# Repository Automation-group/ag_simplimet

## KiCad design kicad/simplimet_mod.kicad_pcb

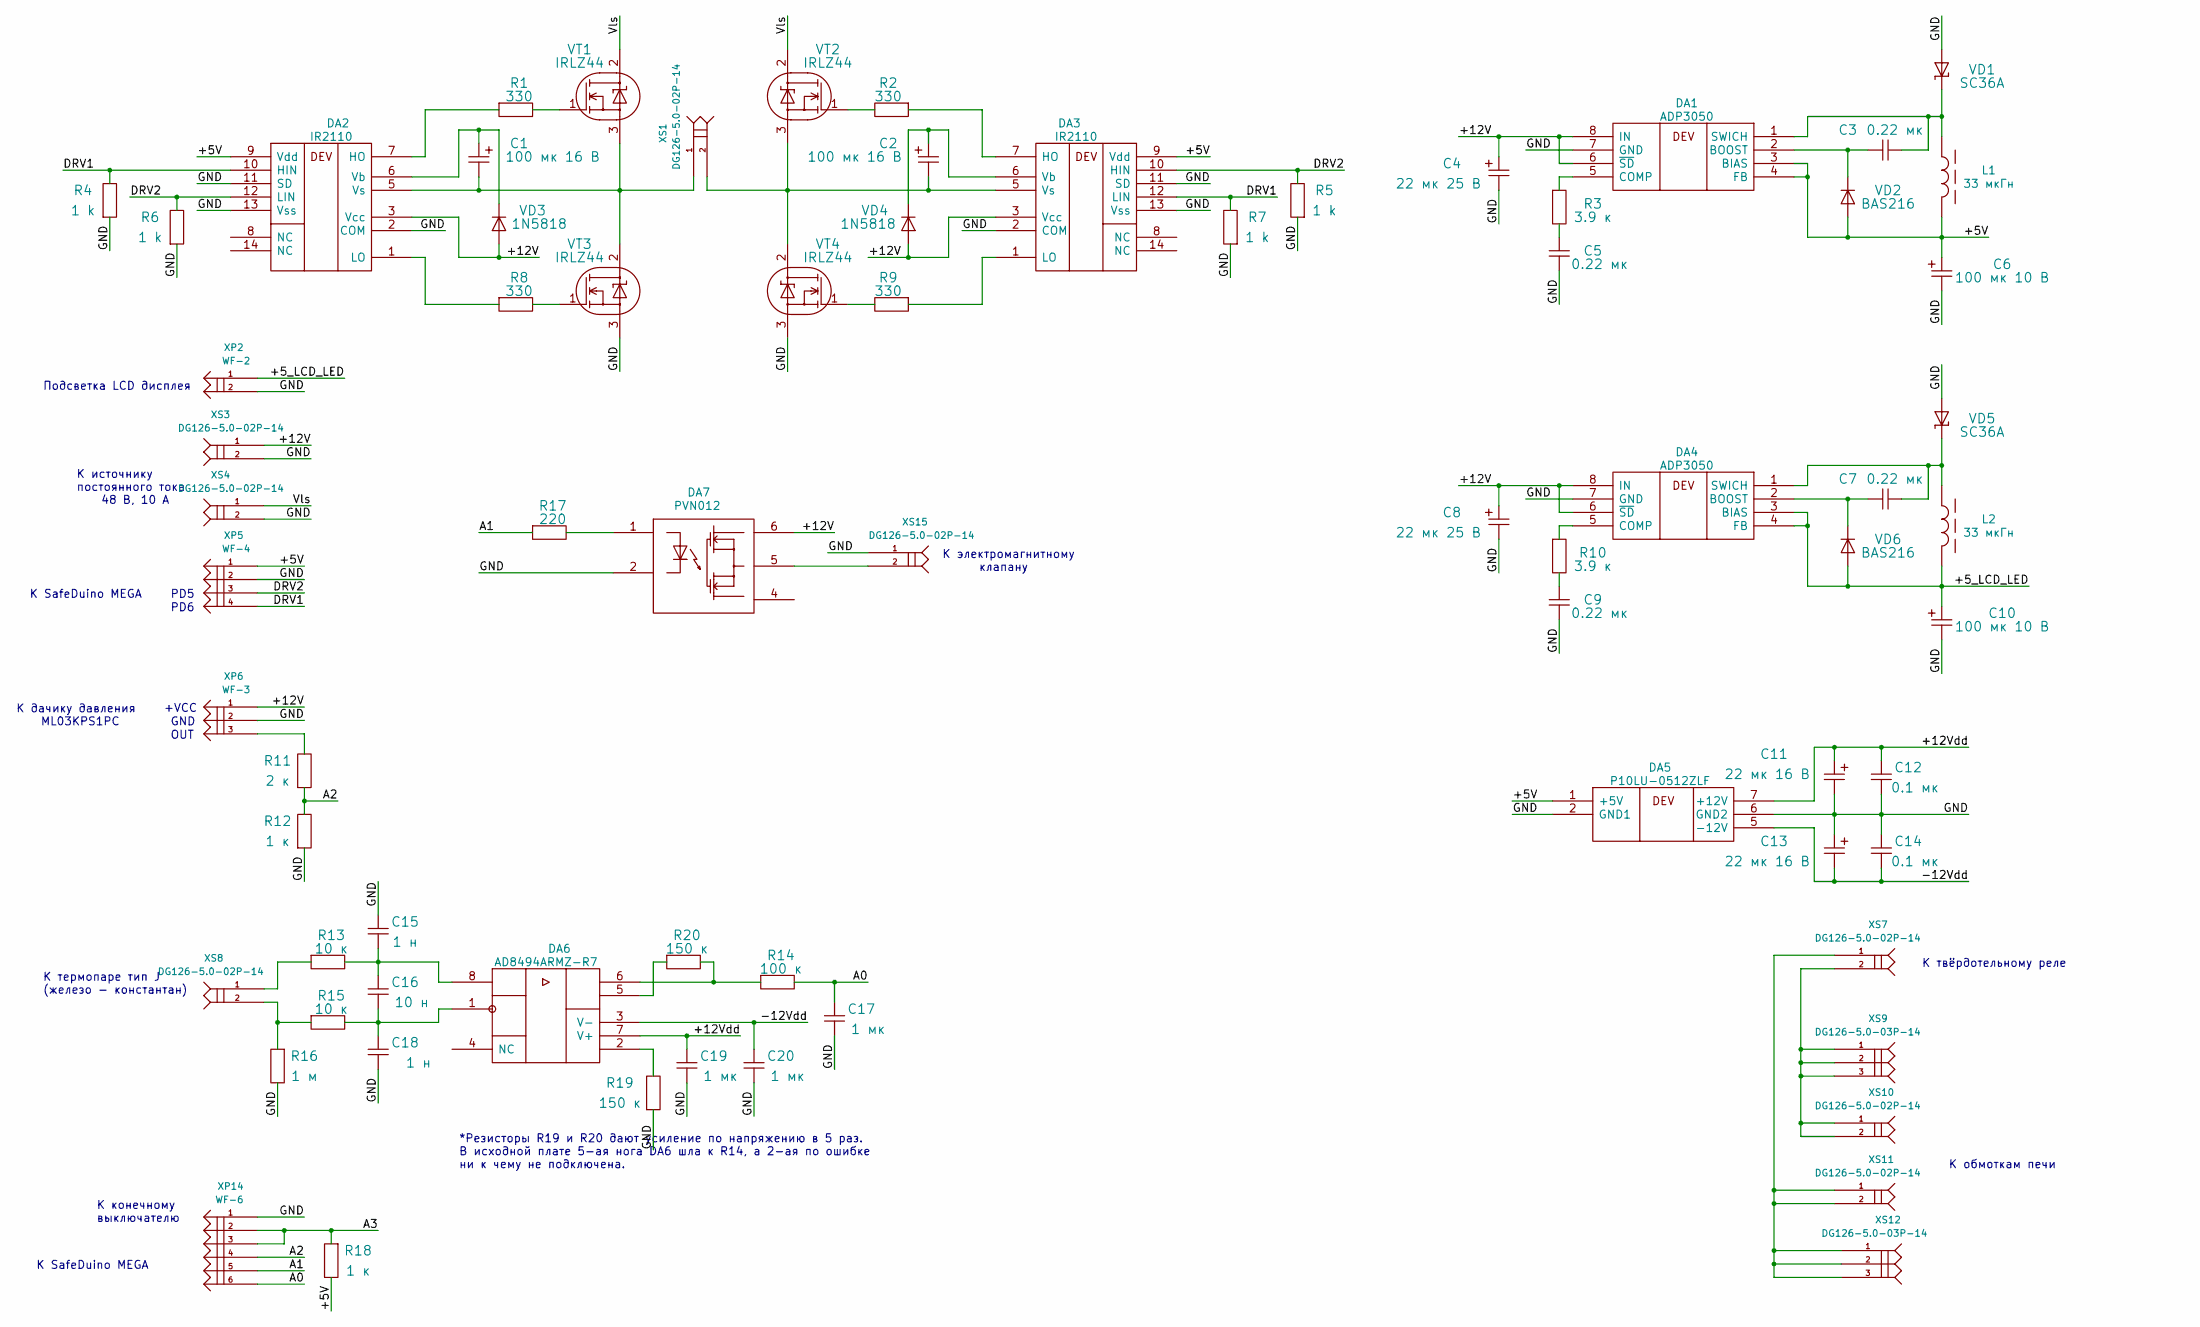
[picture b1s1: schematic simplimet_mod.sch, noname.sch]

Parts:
C1, C2: 100 мк 16 В
C3, C5, C7, C9: 0.22 мк
C4, C8: 22 мк 25 В
C6, C10: 100 мк 10 В
C11, C13: 22 мк 16 В
C12, C14: 0.1 мк
C15, C18: 1 н
C16: 10 н
C17, C19, C20: 1 мк
DA1, DA4: ADP3050
DA2, DA3: IR2110
DA5: P10LU-0512ZLF
DA6: AD8494ARMZ-R7
DA7: PVN012
L1, L2: 33 мкГн
R1, R2, R8, R9: 330
R3, R10: 3.9 к
R4, R5, R6, R7: 1 k
R11: 2 к
R12, R18: 1 к
R13, R15: 10 к
R14: 100 к
R16: 1 м
R17: 220
R19, R20: 150 к
VD1, VD5: SC36A
VD2, VD6: BAS216
VD3, VD4: 1N5818
VT1, VT2, VT3, VT4: IRLZ44
XP2: WF-2
XP5: WF-4
XP6: WF-3
XP14: WF-6
XS1, XS3, XS4, XS7, XS8, XS10, XS11, XS15: DG126-5.0-02P-14
XS9, XS12: DG126-5.0-03P-14

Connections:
/+5V: C6.1, DA1.3 (BIAS), DA1.4 (FB), DA2.9 (Vdd), DA3.9 (Vdd), DA5.1 (+5V), L1.2, R18.2, VD2.1, XP5.1
/+5_LCD_LED: C10.1, DA4.3 (BIAS), DA4.4 (FB), L2.2, VD6.1, XP2.1
/+12V: C4.1, C8.1, DA1.6 (~SD), DA1.8 (IN), DA2.3 (Vcc), DA3.3 (Vcc), DA4.6 (~SD), DA4.8 (IN), DA7.6, VD3.1, VD4.1, XP6.1, XS3.1
/+12Vdd: C11.1, C12.1, C19.1, DA5.7 (+12V), DA6.7 (V+)
/-12Vdd: C13.2, C14.2, C20.1, DA5.5 (-12V), DA6.3 (V-)
/A0: C17.1, R14.2, XP14.6
/A1: R17.1, XP14.5
/A2: R11.1, R12.2, XP14.4
/A3: R18.1, XP14.2, XP14.3
/DRV1: DA2.10 (HIN), DA3.12 (LIN), R4.2, R7.2, XP5.4
/DRV2: DA2.12 (LIN), DA3.10 (HIN), R5.2, R6.2, XP5.3
/GND: C4.2, C5.2, C6.2, C8.2, C9.2, C10.2, C11.2, C12.2, C13.1, C14.1, C15.1, C17.2, C18.2, C19.2, C20.2, DA1.7 (GND), DA2.2 (COM), DA2.11 (SD), DA2.13 (Vss), DA3.2 (COM), DA3.11 (SD), DA3.13 (Vss), DA4.7 (GND), DA5.2 (GND1), DA5.6 (GND2), DA6.2, DA7.2, R4.1, R5.1, R6.1, R7.1, R12.1, R16.2, R19.1, R19.2, VD1.1, VD5.1, VT3.3, VT4.3, XP2.2, XP5.2, XP6.2, XP14.1, XS3.2, XS4.2, XS15.1
/Vls: VT1.2, VT2.2, XS4.1
unnamed: C7.2, DA4.2 (BOOST), VD6.2
unnamed: DA1.5 (COMP), R3.1
unnamed: C5.1, R3.2
unnamed: R11.2, XP6.3
unnamed: C15.2, C16.1, DA6.8, R13.2
unnamed: C16.2, C18.1, DA6.1, R15.2
unnamed: DA4.5 (COMP), R10.1
unnamed: C7.1, DA4.1 (SWICH), L2.1, VD5.2
unnamed: C9.1, R10.2
unnamed: DA3.7 (HO), R2.1
unnamed: R2.2, VT2.1
unnamed: R9.2, VT4.1
unnamed: DA3.1 (LO), R9.1
unnamed: C3.2, DA1.2 (BOOST), VD2.2
unnamed: C3.1, DA1.1 (SWICH), L1.1, VD1.2
unnamed 28: R15.1, R16.1, XS8.2; also elsewhere on the board
unnamed: C2.1, DA3.6 (Vb), VD4.2
unnamed: C2.2, DA3.5 (Vs), VT2.3, VT4.2, XS1.2
unnamed: DA7.5, XS15.2
unnamed: DA7.1, R17.2
unnamed: XS7.1, XS11.1, XS11.2, XS12.1, XS12.2, XS12.3
unnamed 34: R13.1, XS8.1; also elsewhere on the board
unnamed: XS7.2, XS9.1, XS9.2, XS9.3, XS10.1, XS10.2
unnamed: R1.2, VT1.1
unnamed: DA2.1 (LO), R8.1
unnamed: C1.1, DA2.6 (Vb), VD3.2
unnamed: DA2.7 (HO), R1.1
unnamed: C1.2, DA2.5 (Vs), VT1.3, VT3.2, XS1.1
unnamed: R8.2, VT3.1

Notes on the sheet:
К источнику постоянного тока 48 В, 10 А
К SafeDuino MEGA
PD5
PD6
К дачику давления ML03KPS1PC
OUT
+VCC
К термопаре тип J (железо - константан)
К твёрдотельному реле
К обмоткам печи
Подсветка LCD дисплея
GND
К конечному выключателю
К электромагнитному клапану
*Резисторы R19 и R20 дают усиление по напряжению в 5 раз. В исходной плате 5-ая нога DA6 шла к R14, а 2-ая по ошибке ни к чему не подключена.

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
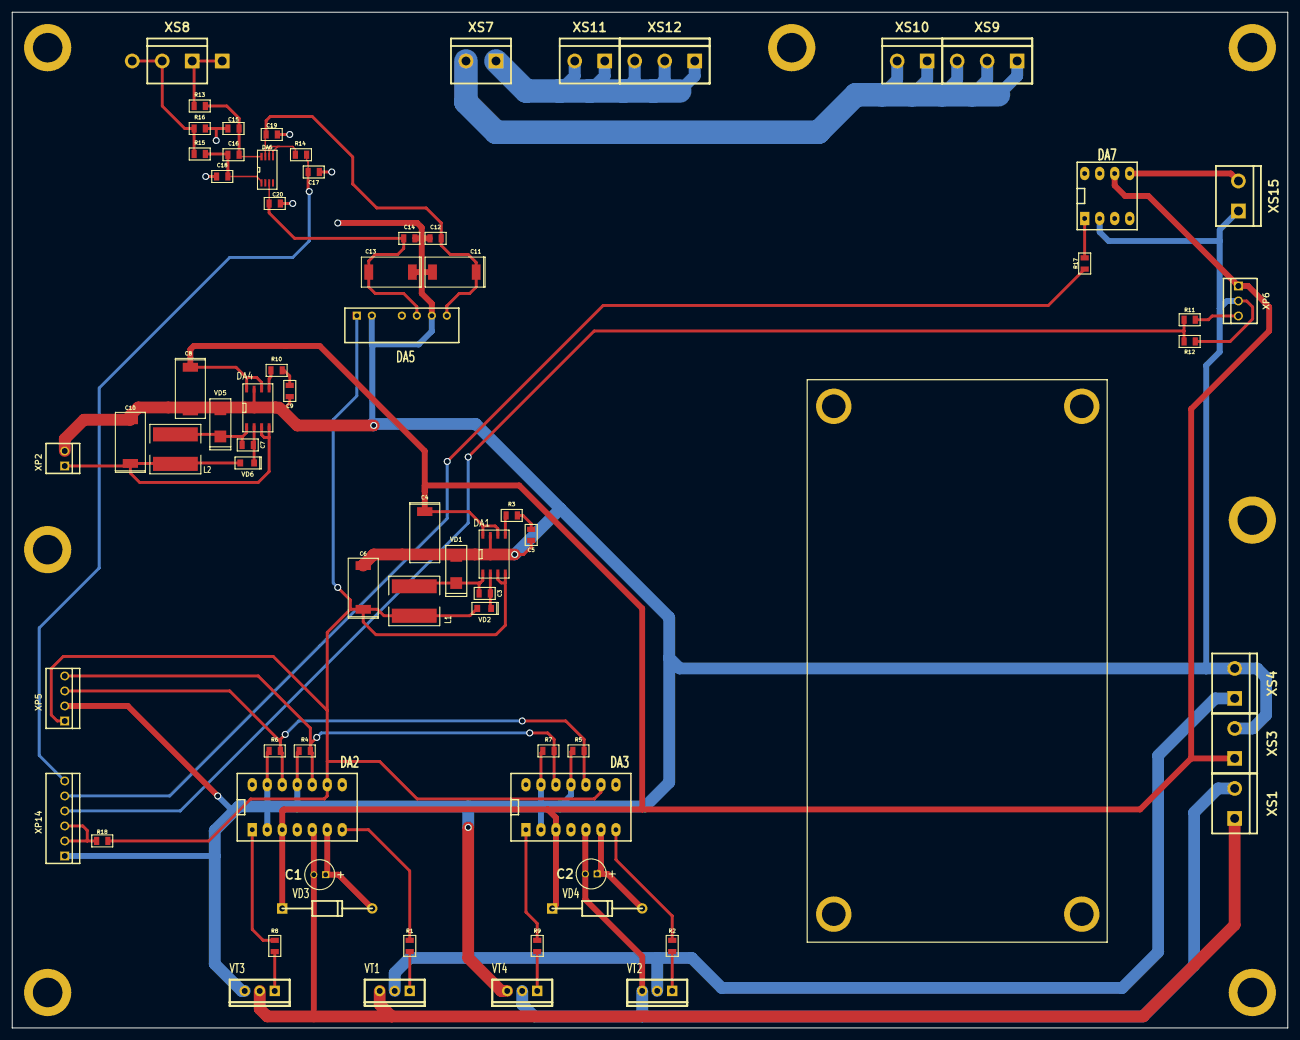
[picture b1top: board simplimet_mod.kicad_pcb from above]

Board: 2 copper layers, 216.0 x 172.0 mm, 84 parts (0 on the bottom side), 43 nets.

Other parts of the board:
1_PIN, 1_PIN#2, 1_PIN#3, 1_PIN#4, 1_PIN#5, 1_PIN#6, 1_PIN#7, 1_PIN#8, 1_PIN#9, 1_PIN#10, 1_PIN#11, 1_PIN#12, 1_PIN#13: P***; 1_pin

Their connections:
unnamed 28: 1_PIN#6.1; also elsewhere on the board
unnamed 34: 1_PIN#5.1; also elsewhere on the board

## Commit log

2015-11-05 Fist commit.
